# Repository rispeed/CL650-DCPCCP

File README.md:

# CL650-DCPCCP
3d printable DCP, and CCP Panels for a challenger 650

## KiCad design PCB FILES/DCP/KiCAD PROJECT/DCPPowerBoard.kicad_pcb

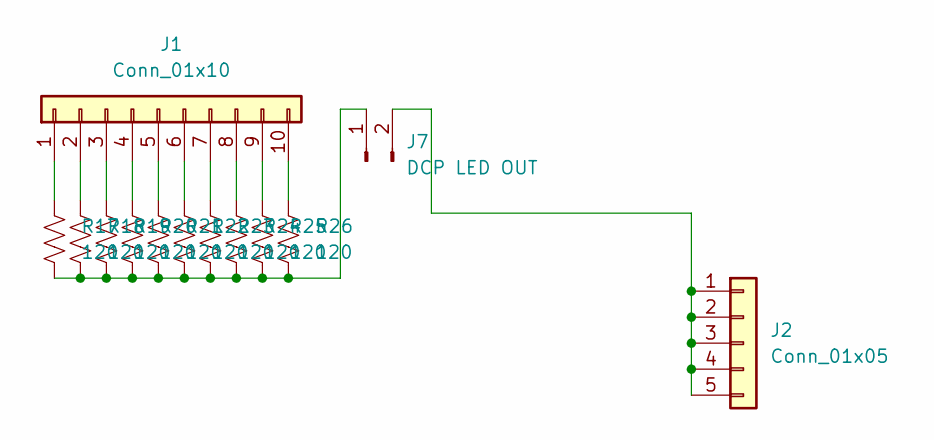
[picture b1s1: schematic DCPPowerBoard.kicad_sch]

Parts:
J1: Conn_01x10; PinHeader_1x10_P2.54mm_Vertical
J2: Conn_01x05; PinHeader_1x05_P2.54mm_Vertical
J7: DCP LED OUT; PinHeader_1x02_P2.54mm_Vertical
R17, R18, R19, R20, R21, R22, R23, R24, R25, R26: 120; R_Axial_DIN0207_L6.3mm_D2.5mm_P10.16mm_Horizontal

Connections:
/<NO NET>: J1.8, R24.1
unnamed: J1.1, R17.1
unnamed: J1.2, R18.1
unnamed: J1.3, R19.1
unnamed: J1.4, R20.1
unnamed: J1.5, R21.1
unnamed: J1.6, R22.1
unnamed: J1.7, R23.1
unnamed: J1.9, R25.1
unnamed: J1.10, R26.1
unnamed: J2.1, J2.2, J2.3, J2.4, J2.5, J7.2
unnamed: J7.1, R17.2, R18.2, R19.2, R20.2, R21.2, R22.2, R23.2, R24.2, R25.2, R26.2

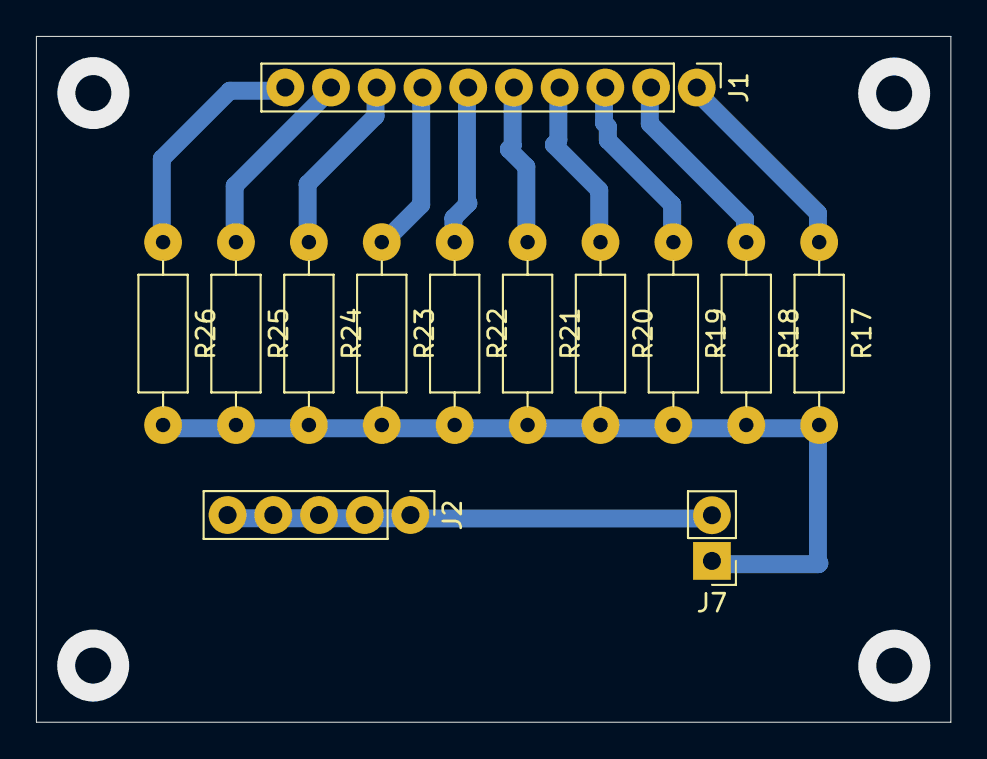
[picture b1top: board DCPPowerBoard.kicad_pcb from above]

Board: 2 copper layers, 50.8 x 38.1 mm, 13 parts (0 on the bottom side), 12 nets.

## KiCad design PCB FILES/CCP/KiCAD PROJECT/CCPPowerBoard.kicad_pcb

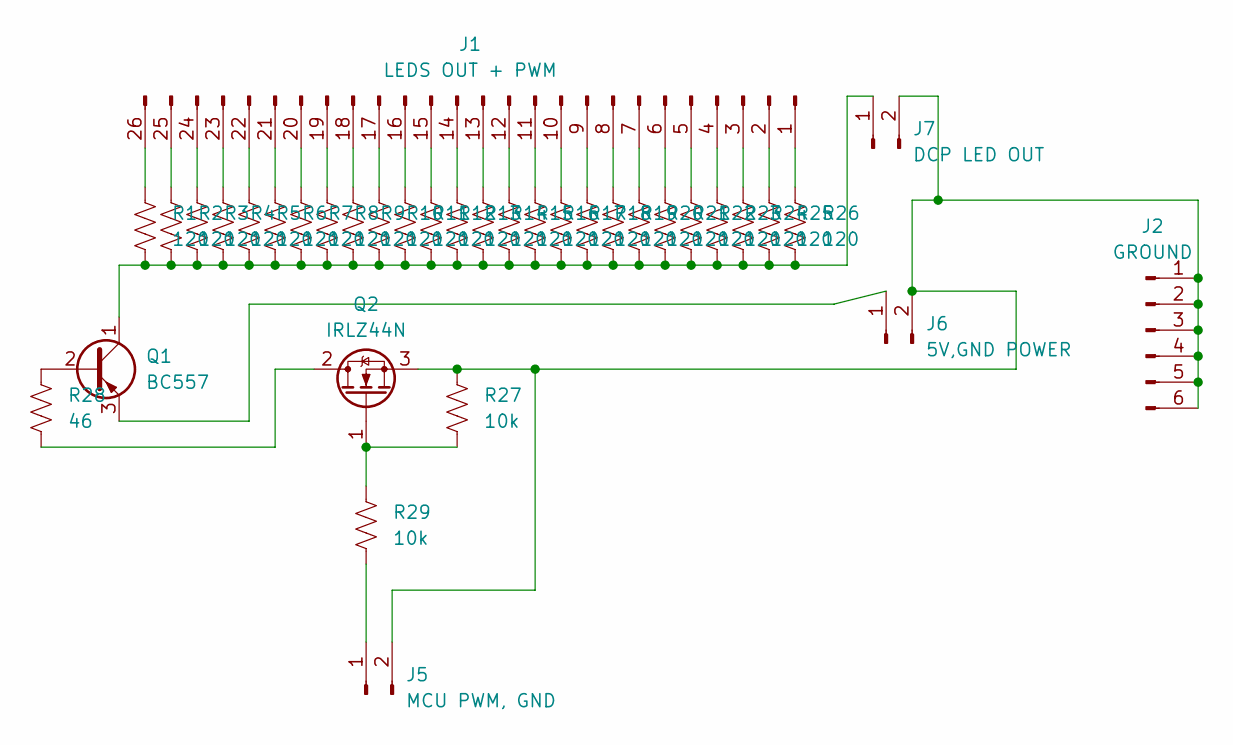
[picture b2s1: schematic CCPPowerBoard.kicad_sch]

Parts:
J1: LEDS OUT + PWM; PinHeader_1x26_P2.54mm_Vertical
J2: GROUND; PinHeader_1x06_P2.54mm_Vertical
J5: MCU PWM, GND; PinHeader_1x02_P2.54mm_Vertical
J6: 5V,GND POWER; PinHeader_1x02_P2.54mm_Vertical
J7: DCP LED OUT; PinHeader_1x02_P2.54mm_Vertical
Q1: BC557; TO-92-3_Formed_Leads
Q2: IRLZ44N; TO-220-3
R1, R2, R3, R4, R5, R6, R7, R8, R9, R10, R11, R12, R13, R14, R15, R16, R17, R18, R19, R20, R21, R22, R23, R24, R25, R26: 120; R_Axial_DIN0207_L6.3mm_D2.5mm_P10.16mm_Horizontal
R27, R29: 10k; R_Axial_DIN0207_L6.3mm_D2.5mm_P10.16mm_Horizontal
R28: 46; R_Axial_DIN0207_L6.3mm_D2.5mm_P10.16mm_Horizontal

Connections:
unnamed: J1.1, R26.1
unnamed: J1.2, R25.1
unnamed: J1.3, R24.1
unnamed: J1.4, R23.1
unnamed: J1.5, R22.1
unnamed: J1.6, R21.1
unnamed: J1.7, R20.1
unnamed: J1.8, R19.1
unnamed: J1.9, R18.1
unnamed: J1.10, R17.1
unnamed: J1.11, R16.1
unnamed: J1.12, R15.1
unnamed: J1.13, R14.1
unnamed: J1.14, R13.1
unnamed: J1.15, R12.1
unnamed: J1.16, R11.1
unnamed: J1.17, R10.1
unnamed: J1.18, R9.1
unnamed: J1.19, R8.1
unnamed: J1.20, R7.1
unnamed: J1.21, R6.1
unnamed: J1.22, R5.1
unnamed: J1.23, R4.1
unnamed: J1.24, R3.1
unnamed: J1.25, R2.1
unnamed: J1.26, R1.1
unnamed: J2.1, J2.2, J2.3, J2.4, J2.5, J2.6, J5.2, J6.2, J7.2, Q2.3 (S), R27.1
unnamed: J5.1, R29.2
unnamed: J6.1, Q1.3 (E)
unnamed: J7.1, Q1.1 (C), R1.2, R2.2, R3.2, R4.2, R5.2, R6.2, R7.2, R8.2, R9.2, R10.2, R11.2, R12.2, R13.2, R14.2, R15.2, R16.2, R17.2, R18.2, R19.2, R20.2, R21.2, R22.2, R23.2, R24.2, R25.2, R26.2
unnamed: Q1.2 (B), R28.1
unnamed: Q2.2 (D), R28.2
unnamed: Q2.1 (G), R27.2, R29.1

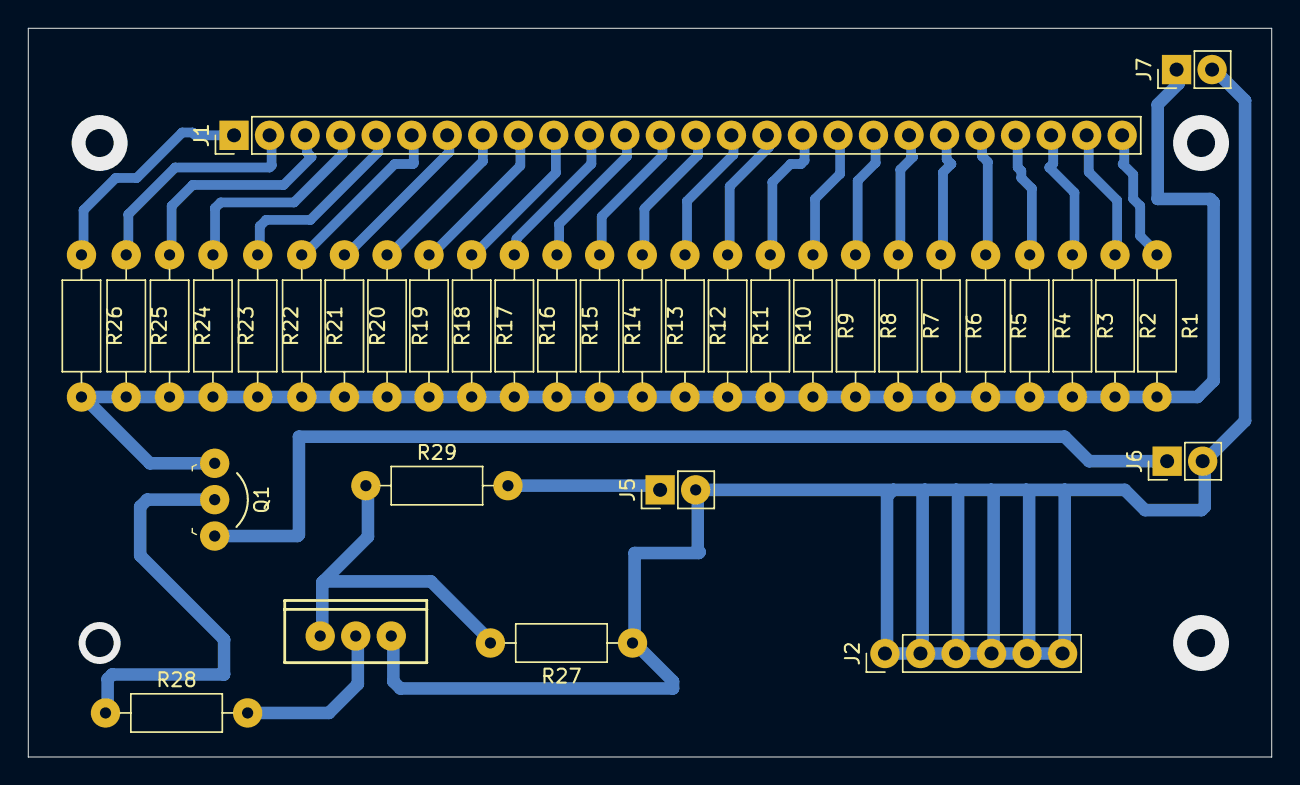
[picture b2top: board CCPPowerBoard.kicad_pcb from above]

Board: 2 copper layers, 88.9 x 52.1 mm, 36 parts (0 on the bottom side), 33 nets.

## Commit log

2024-07-26 Initial
